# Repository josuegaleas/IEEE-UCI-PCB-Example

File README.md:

# IEEE-UCI-PCB-Example
Example project for IEEE UCI's PCB design workshop.

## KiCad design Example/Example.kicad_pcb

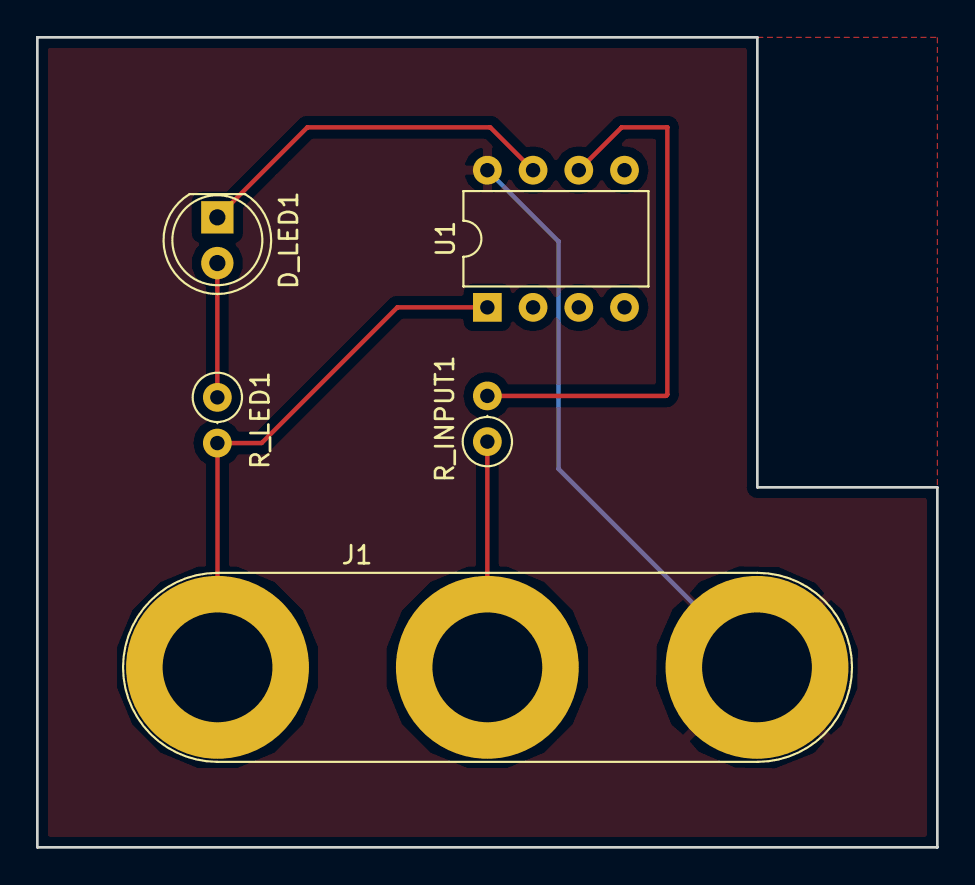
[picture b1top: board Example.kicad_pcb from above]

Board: 2 copper layers, 50.0 x 45.0 mm, 5 parts (0 on the bottom side), 6 nets.

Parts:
D_LED1: LED; LED_D5.0mm
J1: Conn_01x03_Female; Banana_Jack_3Pin
R_INPUT1: 100; R_Axial_DIN0207_L6.3mm_D2.5mm_P2.54mm_Vertical
R_LED1: 1k; R_Axial_DIN0207_L6.3mm_D2.5mm_P2.54mm_Vertical
U1: PIC12C508A-ISN; DIP-8_W7.62mm

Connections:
/Input: R_INPUT1.2, U1.6
GND: J1.3, U1.8
unnamed: D_LED1.1, U1.7
unnamed: D_LED1.2, R_LED1.1
unnamed: J1.2, R_INPUT1.1
VCC: J1.1, R_LED1.2, U1.1

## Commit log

2018-11-27 Blank project
2018-11-27 Symbol schematic complete
2018-11-27 Layout schematic complete
2018-11-27 Gerber files generated
2018-11-29 Added missing ground plane
